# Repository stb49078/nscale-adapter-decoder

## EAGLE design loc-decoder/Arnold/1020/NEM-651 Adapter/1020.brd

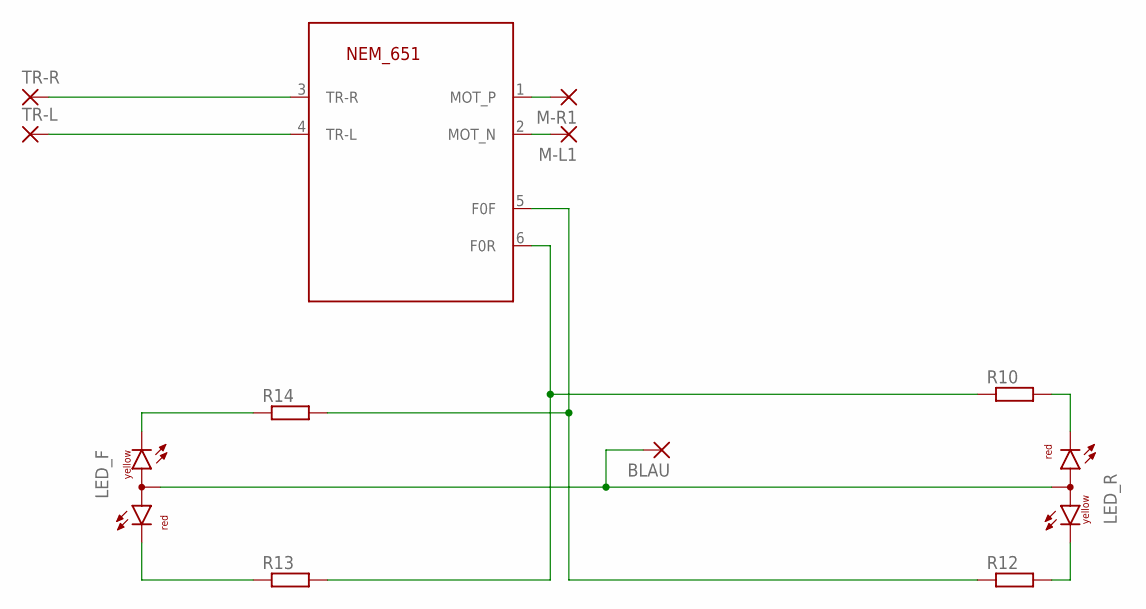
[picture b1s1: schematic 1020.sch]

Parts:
651: NEM_651-TS; 53047-06
BLAU: 1,6/0,8
LED_F: DUOLED-RY-A; DUOLED-A-5MM
LED_R: DUOLED-RY-A; DUOLED-A-5MM
M-L1: SMD5; SMD2,54-5,08
M-R1: SMD5; SMD2,54-5,08
R10, R12, R13, R14: R-EU_R1206; R1206
TR-L: SMD5; SMD2,54-5,08
TR-R: SMD5; SMD2,54-5,08

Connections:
unnamed: BLAU.1, LED_F.A, LED_R.A
unnamed: 651.4 (TR-L), TR-L.1
unnamed: 651.3 (TR-R), TR-R.1
unnamed: 651.5 (F0F), R12.1, R14.2
unnamed: LED_R.CR, R10.2
unnamed: LED_R.CX (CY), R12.2
unnamed: 651.6 (F0R), R10.1, R13.2
unnamed: LED_F.CR, R13.1
unnamed: LED_F.CX (CY), R14.1
unnamed: 651.1 (MOT_P), M-R1.1
unnamed: 651.2 (MOT_N), M-L1.1

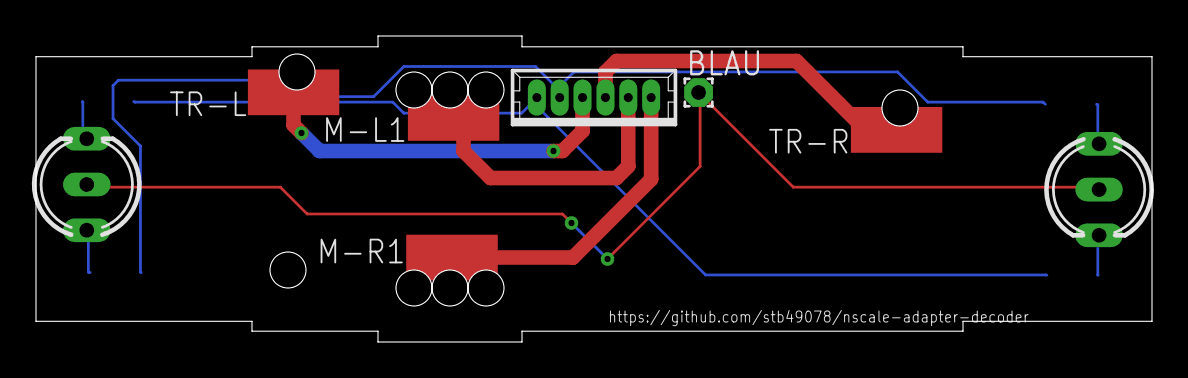
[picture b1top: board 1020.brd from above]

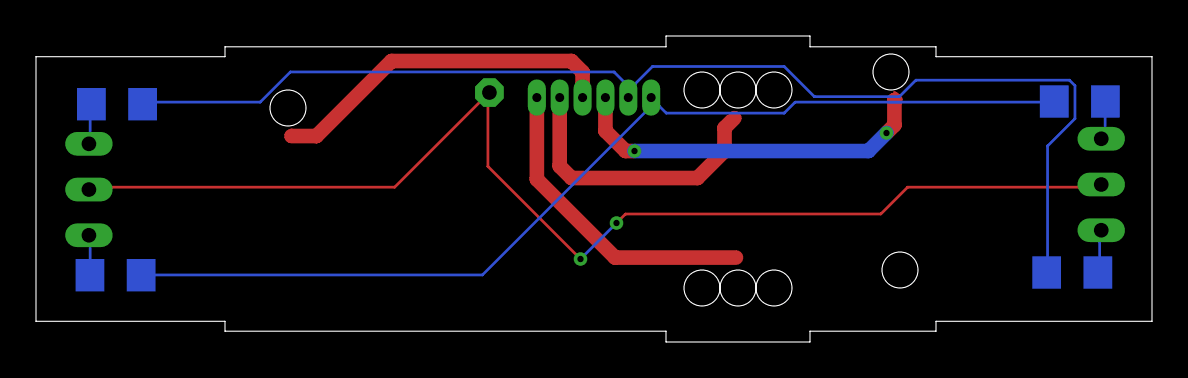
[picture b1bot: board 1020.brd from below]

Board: 2 copper layers, 62.0 x 17.0 mm, 12 parts (4 on the bottom side), 11 nets.

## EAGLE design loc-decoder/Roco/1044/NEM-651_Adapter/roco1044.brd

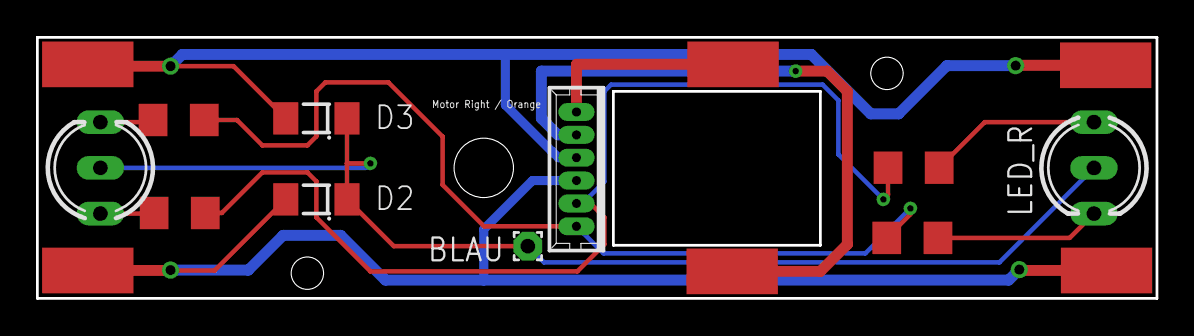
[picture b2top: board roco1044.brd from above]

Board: 2 copper layers, 62.2 x 14.5 mm, 16 parts (0 on the bottom side), 11 nets.

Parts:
651: NEM_651-TS; 53047-06
BLAU: 1,6/0,8
D2, D3: LL4148; SOD80_DO213AA_MINIMELF
LED_F: DUOLED-A-5MM
LED_R: DUOLED-A-5MM
M-L: SMD2,54-5,08
M-R: SMD2,54-5,08
R1, R2, R3, R4: R1206
TR-L-1, TR-L-2: SMD2,54-5,08
TR-R-1, TR-R-2: SMD2,54-5,08

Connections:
M-L: 651.2, M-L.1
M-R: 651.1, M-R.1
unnamed: BLAU.1, D2.C, D3.C, LED_F.A, LED_R.A
unnamed: 651.4, D2.A, TR-L-1.1, TR-L-2.1
unnamed: 651.3, D3.A, TR-R-1.1, TR-R-2.1
unnamed: 651.5, R2.1, R4.2
unnamed: LED_R.CR, R1.2
unnamed: LED_R.CX, R2.2
unnamed: 651.6, R1.1, R3.2
unnamed: LED_F.CR, R3.1
unnamed: LED_F.CX, R4.1

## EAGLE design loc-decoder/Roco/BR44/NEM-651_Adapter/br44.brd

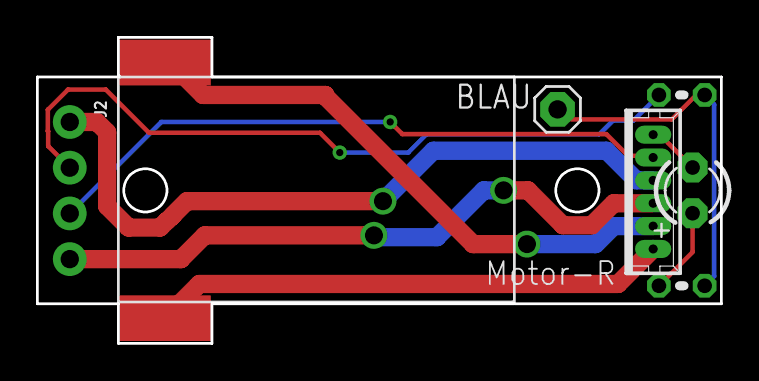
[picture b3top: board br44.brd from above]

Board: 2 copper layers, 38.0 x 17.0 mm, 8 parts (0 on the bottom side), 9 nets.

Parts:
BLAU: 1X01
J2: 1X04_NO_SILK
LED2: LED3MM
PAD1, PAD2: SMD2,54-5,08
R3, R4: 1k; 0204V
U$1: NEM_651-TS; 53047-06

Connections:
unnamed: PAD1.1, U$1.1
unnamed: PAD2.1, U$1.2
unnamed: J2.4, U$1.3
unnamed: J2.1, U$1.4
unnamed: BLAU.1, R3.2, R4.2
unnamed: LED2.A, R4.1
unnamed: J2.2, R3.1
unnamed: J2.3, U$1.5
unnamed: LED2.K, U$1.6

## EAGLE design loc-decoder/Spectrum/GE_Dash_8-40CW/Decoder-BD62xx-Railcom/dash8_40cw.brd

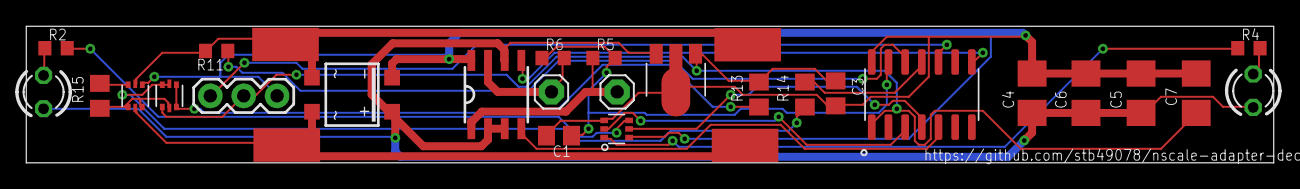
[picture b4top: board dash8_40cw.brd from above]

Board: 2 copper layers, 95.0 x 10.4 mm, 30 parts (0 on the bottom side), 23 nets.

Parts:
B1: MB1S; SOIC-4
C1: 0.1u; C0805
C3: 100n; C0805
C4, C5, C6, C7: CT3528
IC1: 78L05F; SOT89
IC2: BD6230F; SOP8
J2: 455-1750-1-ND; 1X03
LED1, LED2: LED3MM
M-L: 1X01
M-R: 1X01
R2, R4: 1k; R0603
R5, R6: 10k; R0603
R11: 3k3; R0603
R13: 22; R0805
R14: 10k; R0805
R15: 6k8; R0805
TR-L-1, TR-L-2: SMD2,54-5,08
TR-R-1, TR-R-2: SMD2,54-5,08
U2: ATTINY1614-SSNR; SOIC127P600X175-14N
U$1: DMN65D8LDW; SOT363
U$3: BC857BV; SOT-666
U$4: BC847BV; SOT-666

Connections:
+5V: C3.1, C7.+, IC1.1, J2.2, R13.2, U2.1, U$3.P$1
BEMF: C1.1, R5.2, R6.1, U2.13
COMMAND: R11.1, U2.12
FORWARD: IC2.4, U2.5
GND: B1.-, C1.2, C3.2, C4.-, C5.-, C6.-, C7.-, IC1.2, IC1.2@1, IC2.8, J2.1, U2.14, U$1.P$3, U$1.P$6, U$4.P$4
LIGHT-B: U2.4, U$1.P$5
LIGHT-F: U2.3, U$1.P$2
M-L: IC2.1, M-L.1, R5.1
M-R: IC2.7, M-R.1, R6.2
unnamed: LED2.K, R2.1
unnamed: R4.1, U$1.P$1
unnamed: R2.2, U$1.P$4
unnamed: LED1.K, R4.2
unnamed: R15.2, U$4.P$5
unnamed: R15.1, U$3.P$3, U$4.P$1, U$4.P$2
unnamed: R13.1, U$3.P$2, U$3.P$4
unnamed: R14.1, U$3.P$5, U$3.P$6
RAILCOM: R14.2, U2.11
REVERSE: IC2.5, U2.8
RST/UDPI: J2.3, U2.10
TR-L: B1.~1, R11.2, TR-L-1.1, TR-L-2.1, U$4.P$6
TR-R: B1.~2, TR-R-1.1, TR-R-2.1, U$4.P$3
V+: B1.+, C4.+, C5.+, C6.+, IC1.3, IC2.2, IC2.3, IC2.6, LED1.A, LED2.A

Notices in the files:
parts and their libraries:
SparkFun-Connectors: Licensing: Creative Commons ShareAlike 4.0 International - https://creativecommons.org/licenses/by-sa/4.0
